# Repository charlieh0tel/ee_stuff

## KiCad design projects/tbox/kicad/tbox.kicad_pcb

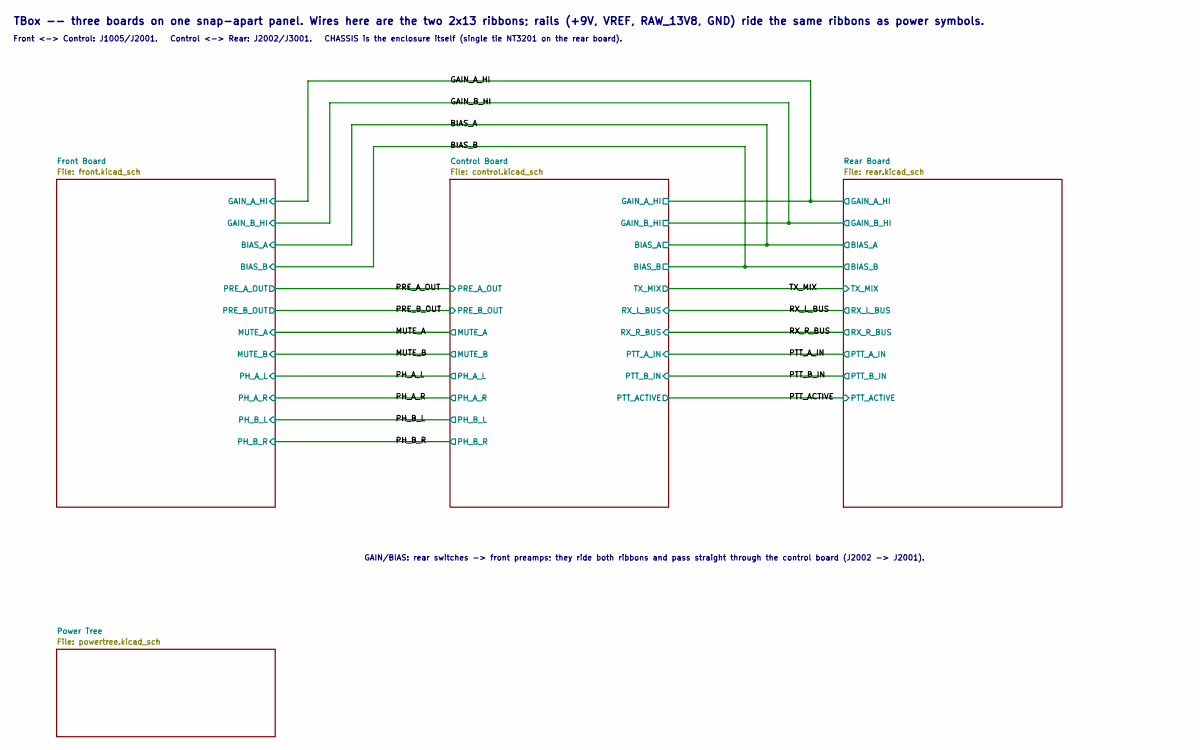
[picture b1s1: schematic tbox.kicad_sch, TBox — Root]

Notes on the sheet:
Front <-> Control: J1005/J2001. Control <-> Rear: J2002/J3001. CHASSIS is the enclosure itself (single tie NT3201 on the rear board).
GAIN/BIAS: rear switches -> front preamps; they ride both ribbons and pass straight through the control board (J2002 -> J2001).
TBox -- three boards on one snap-apart panel. Wires here are the two 2x13 ribbons; rails (+9V, VREF, RAW_13V8, GND) ride the same ribbons as power symbols.

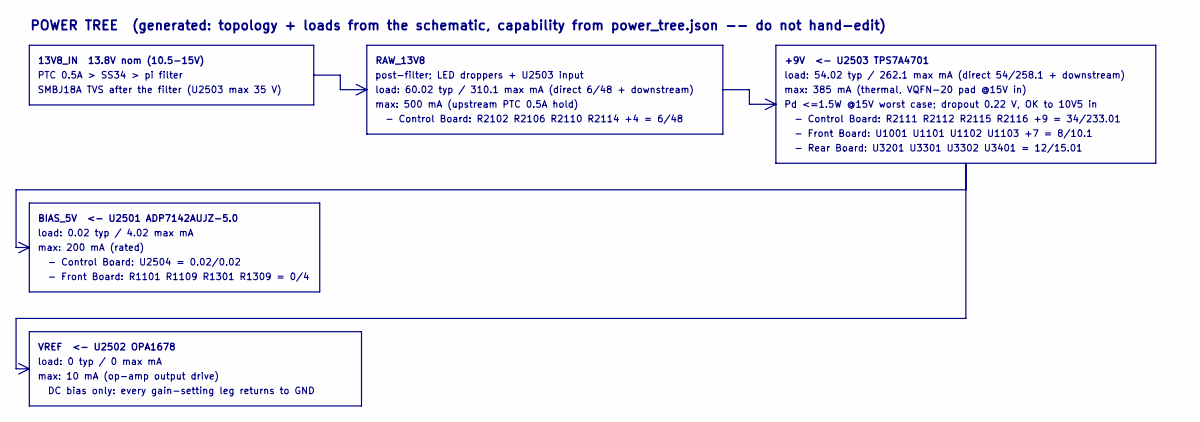
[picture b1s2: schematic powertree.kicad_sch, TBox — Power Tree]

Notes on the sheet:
POWER TREE (generated: topology + loads from the schematic, capability from power_tree.json -- do not hand-edit)
13V8_IN 13.8V nom (10.5-15V)
PTC 0.5A > SS34 > pi filter
SMBJ18A TVS after the filter (U2503 max 35 V)
RAW_13V8
post-filter; LED droppers + U2503 input
load: 60.02 typ / 310.1 max mA (direct 6/48 + downstream)
max: 500 mA (upstream PTC 0.5A hold)
- Control Board: R2102 R2106 R2110 R2114 +4 = 6/48
+9V <- U2503 TPS7A4701
load: 54.02 typ / 262.1 max mA (direct 54/258.1 + downstream)
max: 385 mA (thermal, VQFN-20 pad @15V in)
Pd <=1.5W @15V worst case; dropout 0.22 V, OK to 10V5 in
- Control Board: R2111 R2112 R2115 R2116 +9 = 34/233.01
- Front Board: U1001 U1101 U1102 U1103 +7 = 8/10.1
- Rear Board: U3201 U3301 U3302 U3401 = 12/15.01
BIAS_5V <- U2501 ADP7142AUJZ-5.0
load: 0.02 typ / 4.02 max mA
max: 200 mA (rated)
- Control Board: U2504 = 0.02/0.02
- Front Board: R1101 R1109 R1301 R1309 = 0/4
VREF <- U2502 OPA1678
load: 0 typ / 0 max mA
max: 10 mA (op-amp output drive)
DC bias only: every gain-setting leg returns to GND

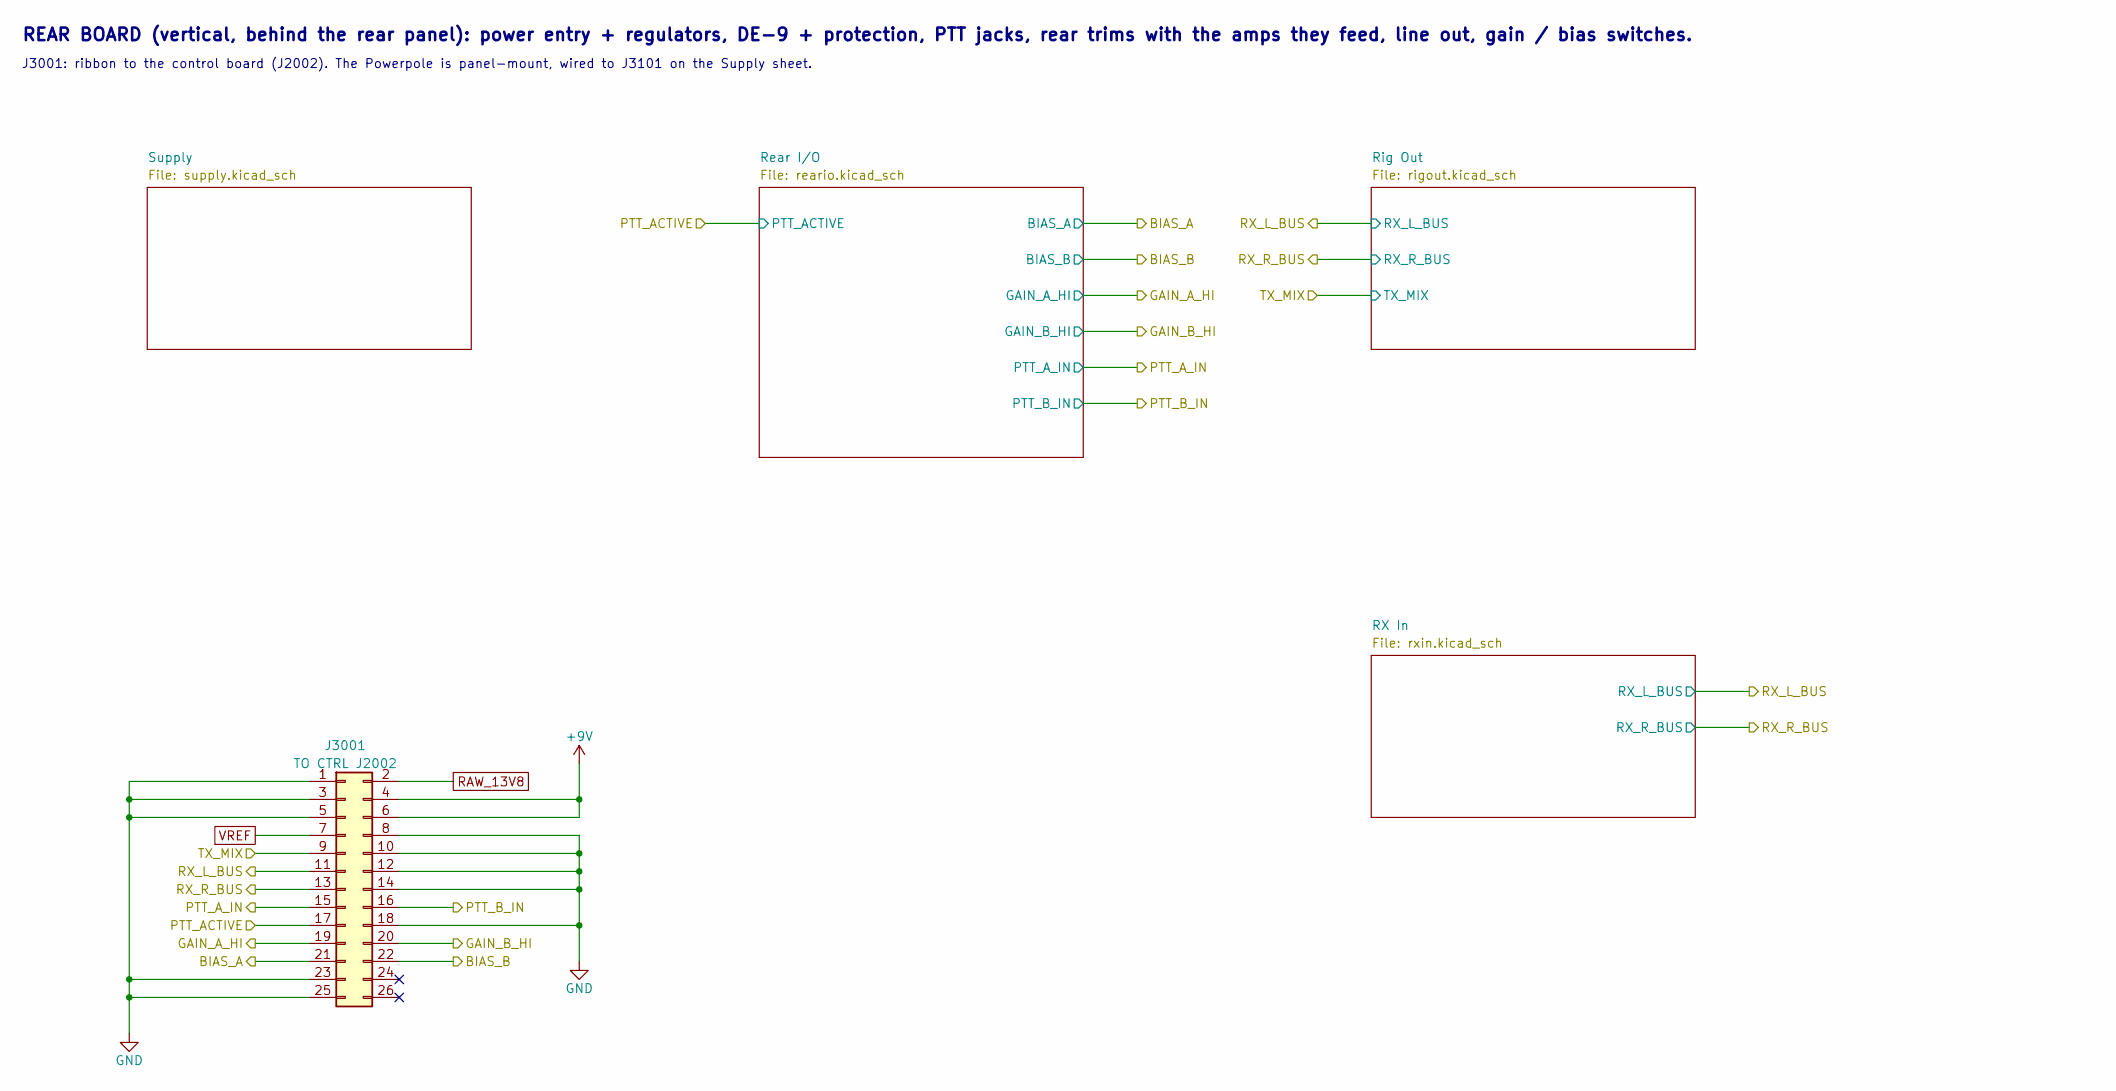
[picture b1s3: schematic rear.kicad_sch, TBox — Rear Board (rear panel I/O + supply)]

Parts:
J3001: TO CTRL J2002; IDC-Header_2x13_P2.54mm_Vertical; MPN IDC 2x13 box header

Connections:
+9V: J3001.4, J3001.6; also elsewhere on the board
/BIAS_A: J3001.21; also elsewhere on the board
/BIAS_B: J3001.22; also elsewhere on the board
/GAIN_A_HI: J3001.19; also elsewhere on the board
/GAIN_B_HI: J3001.20; also elsewhere on the board
/PTT_ACTIVE: J3001.17; also elsewhere on the board
/PTT_A_IN: J3001.15; also elsewhere on the board
/PTT_B_IN: J3001.16; also elsewhere on the board
/RX_L_BUS: J3001.11; also elsewhere on the board
/RX_R_BUS: J3001.13; also elsewhere on the board
/TX_MIX: J3001.9; also elsewhere on the board

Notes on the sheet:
REAR BOARD (vertical, behind the rear panel): power entry + regulators, DE-9 + protection, PTT jacks, rear trims with the amps they feed, line out, gain / bias switches.
J3001: ribbon to the control board (J2002). The Powerpole is panel-mount, wired to J3101 on the Supply sheet.

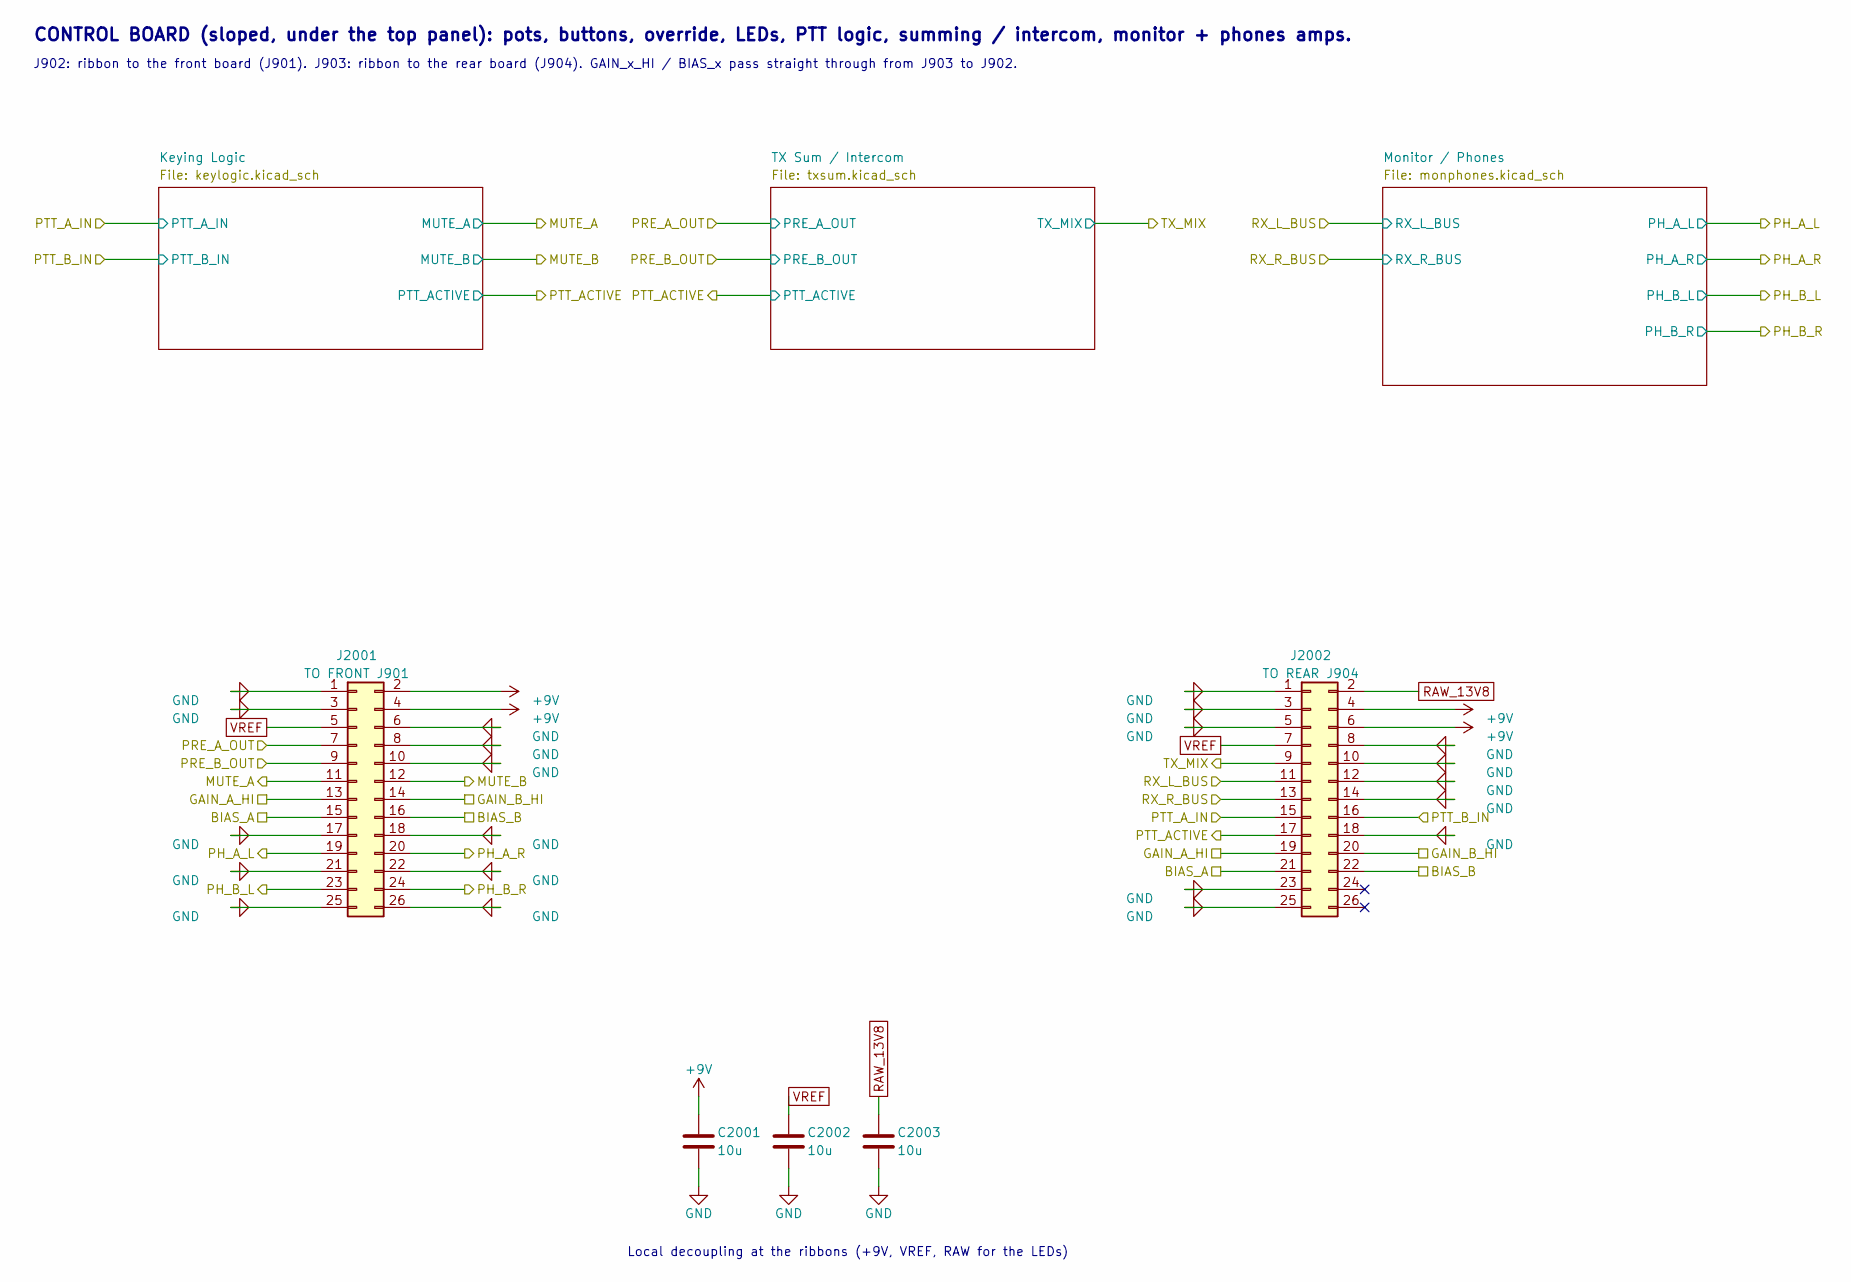
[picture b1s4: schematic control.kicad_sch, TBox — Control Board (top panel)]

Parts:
C2001, C2002, C2003: 10u
J2001: TO FRONT J901
J2002: TO REAR J904

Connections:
+9V: C2001.1, J2001.2, J2001.4, J2002.4, J2002.6; also elsewhere on the board
/BIAS_A: J2001.15, J2002.21; also elsewhere on the board
/BIAS_B: J2001.16, J2002.22; also elsewhere on the board
/GAIN_A_HI: J2001.13, J2002.19; also elsewhere on the board
/GAIN_B_HI: J2001.14, J2002.20; also elsewhere on the board
/MUTE_B: J2001.12; also elsewhere on the board
/PH_A_L: J2001.19; also elsewhere on the board
/PH_A_R: J2001.20; also elsewhere on the board
/PH_B_L: J2001.23; also elsewhere on the board
/PH_B_R: J2001.24; also elsewhere on the board
/PRE_A_OUT: J2001.7; also elsewhere on the board
/PRE_B_OUT: J2001.9; also elsewhere on the board
/PTT_ACTIVE: J2002.17; also elsewhere on the board
/PTT_A_IN: J2002.15; also elsewhere on the board
/PTT_B_IN: J2002.16; also elsewhere on the board
/RX_L_BUS: J2002.11; also elsewhere on the board
/RX_R_BUS: J2002.13; also elsewhere on the board
/TX_MIX: J2002.9; also elsewhere on the board

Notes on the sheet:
Local decoupling at the ribbons (+9V, VREF, RAW for the LEDs)
CONTROL BOARD (sloped, under the top panel): pots, buttons, override, LEDs, PTT logic, summing / intercom, monitor + phones amps.
J902: ribbon to the front board (J901). J903: ribbon to the rear board (J904). GAIN_x_HI / BIAS_x pass straight through from J903 to J902.

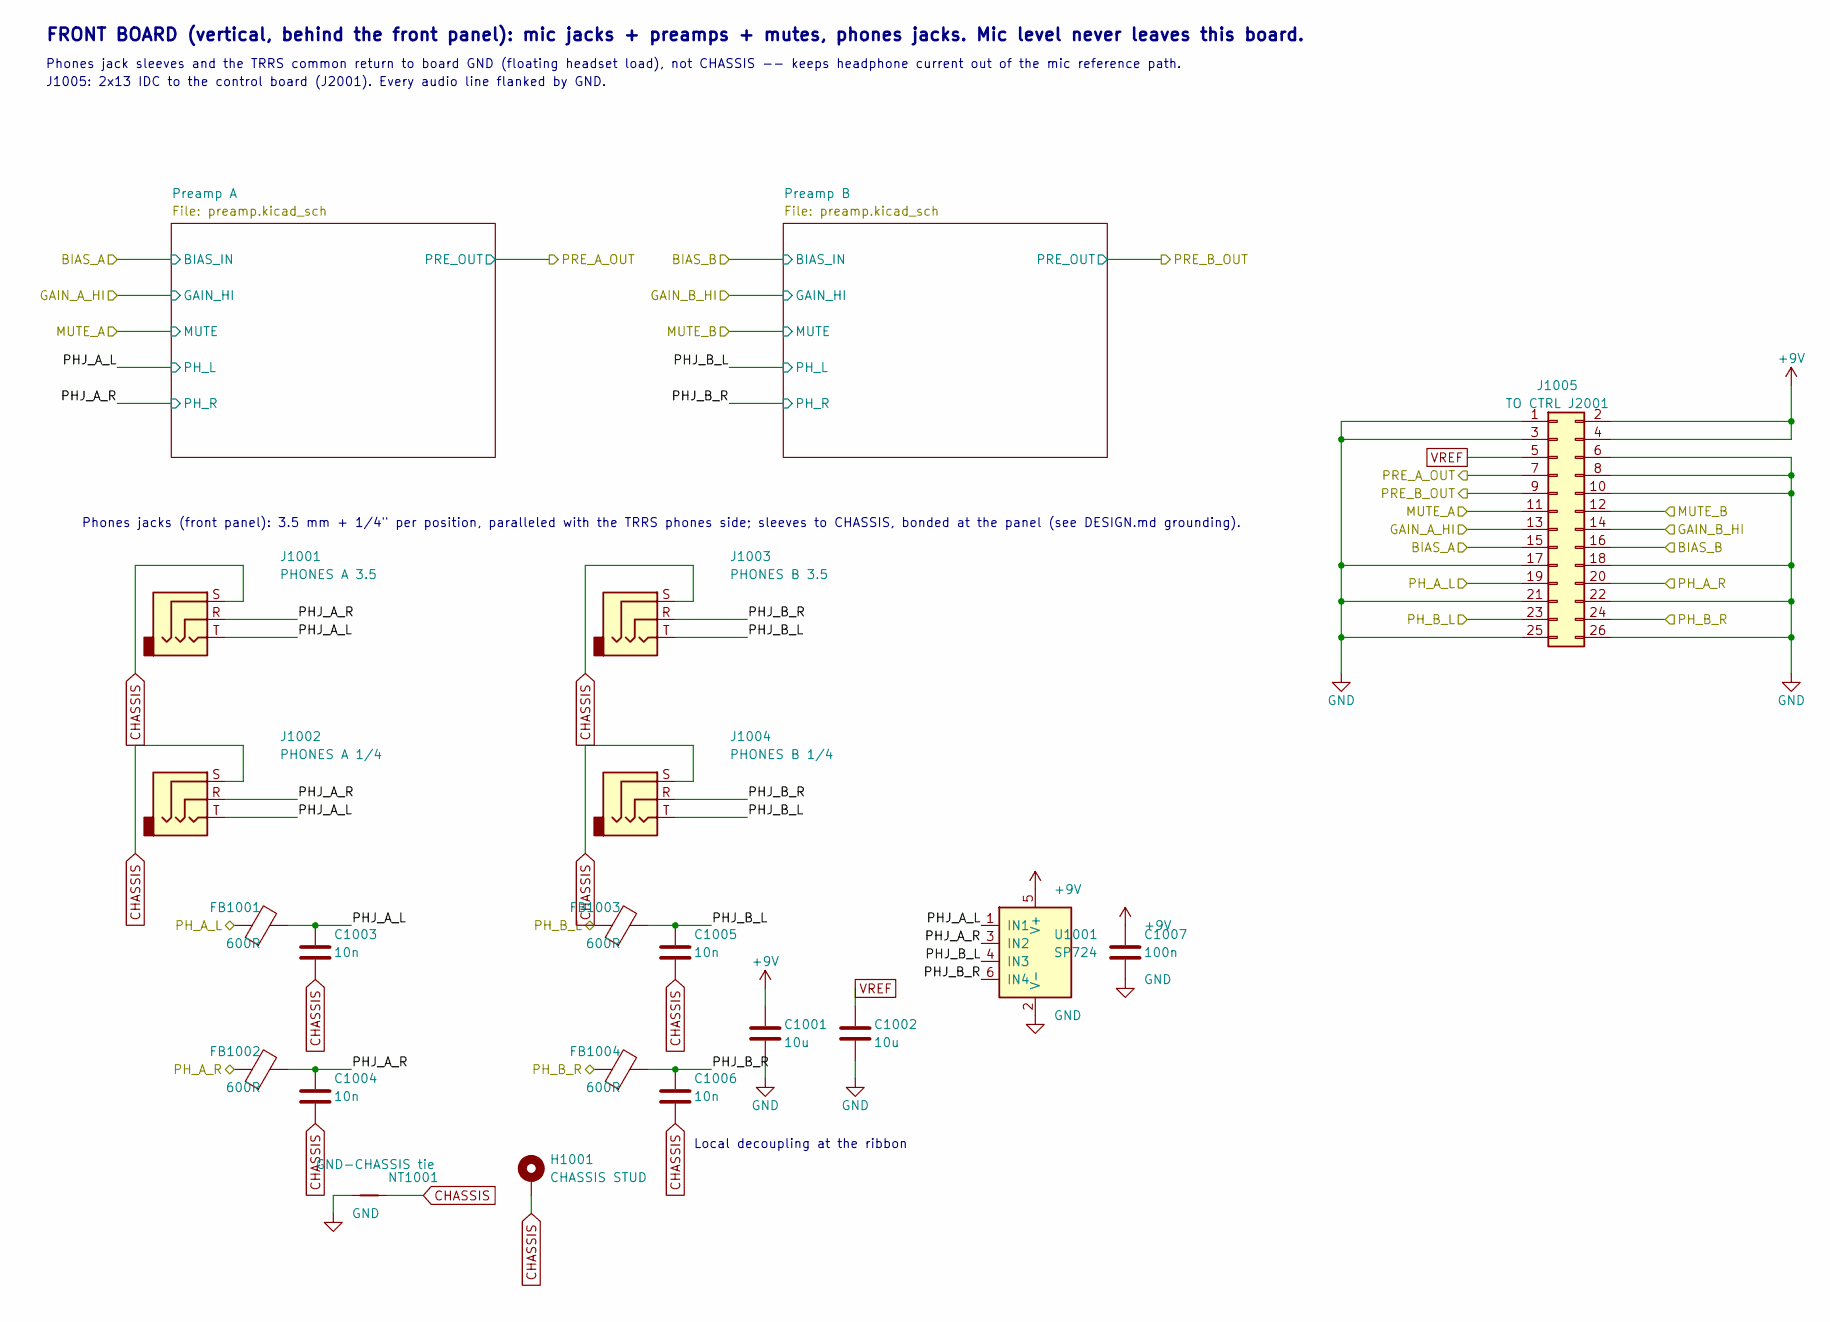
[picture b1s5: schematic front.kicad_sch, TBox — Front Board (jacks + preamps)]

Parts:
C1001, C1002: 10u; C_1206_3216Metric
C1003, C1004, C1005, C1006: 10n; C_0603_1608Metric
C1007: 100n; C_0603_1608Metric
FB1001, FB1002, FB1003, FB1004: 600R; L_0805_2012Metric; MPN BLM21PG601SN1D
H1001: CHASSIS STUD; MountingHole_3.2mm_M3_Pad
J1001: PHONES A 3.5; Jack_3.5mm_CUI_SJ1-3533NG_Horizontal; MPN SJ1-3533NG
J1002: PHONES A 1/4; Jack_6.35mm_Neutrik_NRJ6HF-1_Horizontal; MPN NRJ6HF-1
J1003: PHONES B 3.5; Jack_3.5mm_CUI_SJ1-3533NG_Horizontal; MPN SJ1-3533NG
J1004: PHONES B 1/4; Jack_6.35mm_Neutrik_NRJ6HF-1_Horizontal; MPN NRJ6HF-1
J1005: TO CTRL J2001; IDC-Header_2x13_P2.54mm_Vertical; MPN IDC 2x13 box header
NT1001: GND-CHASSIS tie; NetTie-2_SMD_Pad0.5mm
U1001: SP724; SOT-23-6; MPN SP724AHTG

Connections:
+9V: C1001.1, C1007.1, J1005.2, J1005.4, U1001.5 (V+); also elsewhere on the board
/BIAS_A: J1005.15; also elsewhere on the board
/BIAS_B: J1005.16; also elsewhere on the board
/Front Board/PHJ_A_L: C1003.1, FB1001.2, J1001.T, J1002.T, U1001.1 (IN1); also elsewhere on the board
/Front Board/PHJ_A_R: C1004.1, FB1002.2, J1001.R, J1002.R, U1001.3 (IN2); also elsewhere on the board
/Front Board/PHJ_B_L: C1005.1, FB1003.2, J1003.T, J1004.T, U1001.4 (IN3); also elsewhere on the board
/Front Board/PHJ_B_R: C1006.1, FB1004.2, J1003.R, J1004.R, U1001.6 (IN4); also elsewhere on the board
/GAIN_A_HI: J1005.13; also elsewhere on the board
/GAIN_B_HI: J1005.14; also elsewhere on the board
/MUTE_B: J1005.12; also elsewhere on the board
/PH_A_L: FB1001.1, J1005.19; also elsewhere on the board
/PH_A_R: FB1002.1, J1005.20; also elsewhere on the board
/PH_B_L: FB1003.1, J1005.23; also elsewhere on the board
/PH_B_R: FB1004.1, J1005.24; also elsewhere on the board
/PRE_A_OUT: J1005.7; also elsewhere on the board
/PRE_B_OUT: J1005.9; also elsewhere on the board

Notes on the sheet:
J1005: 2x13 IDC to the control board (J2001). Every audio line flanked by GND.
Phones jacks (front panel): 3.5 mm + 1/4" per position, paralleled with the TRRS phones side; sleeves to CHASSIS, bonded at the panel (see DESIGN.md grounding).
Phones jack sleeves and the TRRS common return to board GND (floating headset load), not CHASSIS -- keeps headphone current out of the mic reference path.
FRONT BOARD (vertical, behind the front panel): mic jacks + preamps + mutes, phones jacks. Mic level never leaves this board.
Local decoupling at the ribbon

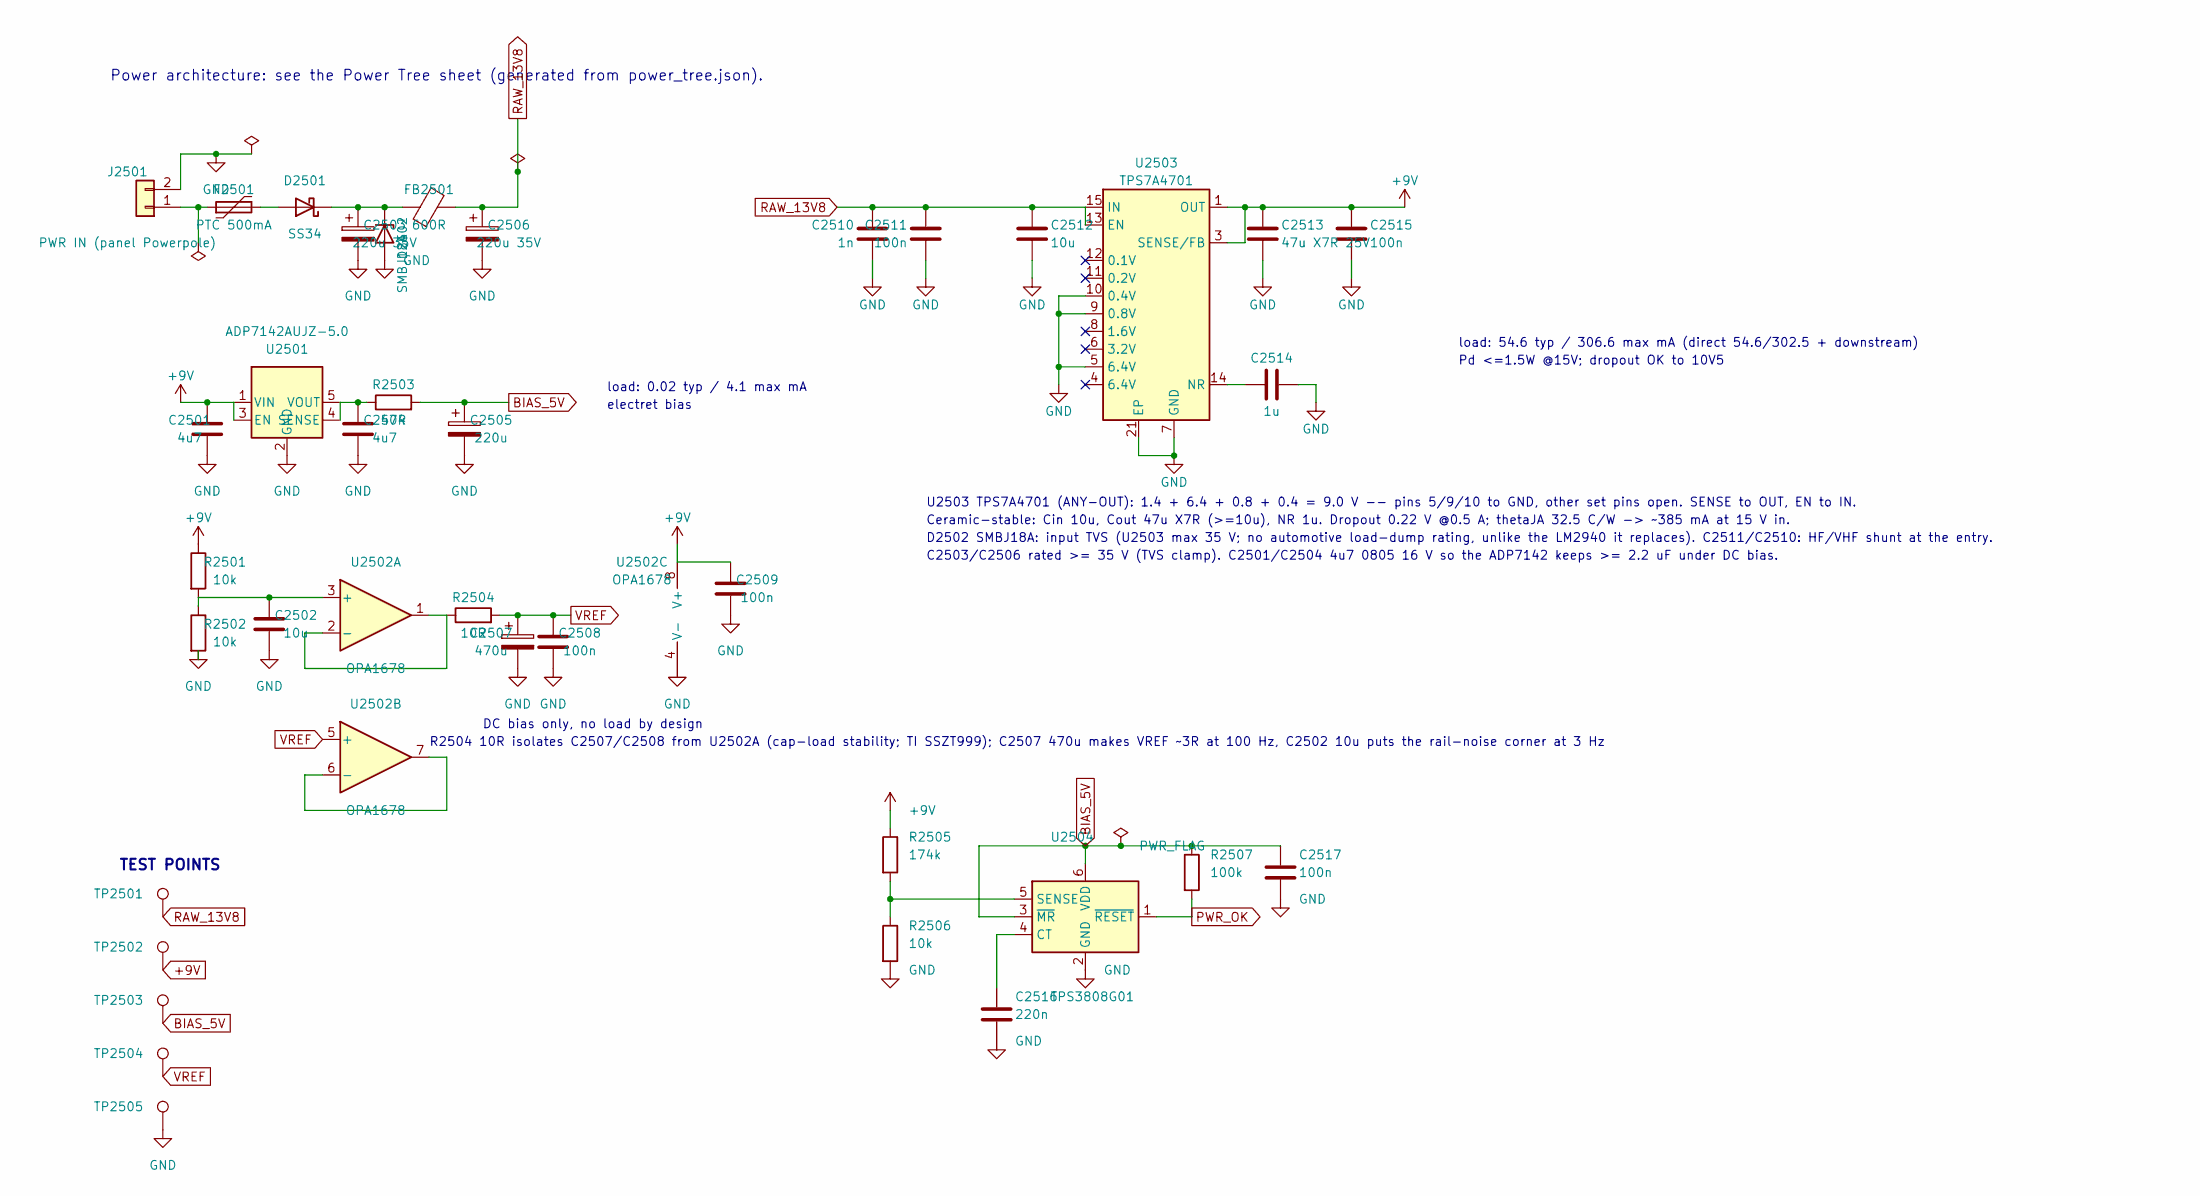
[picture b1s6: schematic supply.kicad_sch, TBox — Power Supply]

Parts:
C2501, C2504: 4u7; C_0805_2012Metric
C2502, C2512: 10u; C_1206_3216Metric
C2503, C2506: 220u 35V; CP_Elec_10x10.5
C2505: 220u; CP_Elec_8x10.5
C2507: 470u; CP_Elec_10x10.5
C2508, C2509, C2511, C2515, C2517: 100n; C_0603_1608Metric
C2510: 1n; C_0603_1608Metric
C2513: 47u X7R 25V; C_1210_3225Metric; MPN GRM32ER71E476KE15L
C2514: 1u; C_0603_1608Metric
C2516: 220n; C_0603_1608Metric
D2501: SS34; D_SMA; MPN SS34
D2502: SMBJ18A; D_SMB; MPN SMBJ18A
F2501: PTC 500mA; Fuse_1812_4532Metric; MPN 1812L050/60MR
FB2501: 600R; L_0805_2012Metric; MPN BLM21PG601SN1D
J2501: PWR IN (panel Powerpole); JST_XH_B2B-XH-A_1x02_P2.50mm_Vertical; MPN B2B-XH-A
R2501, R2502, R2506: 10k; R_0603_1608Metric
R2503: 47R; R_0603_1608Metric
R2504: 10R; R_0603_1608Metric
R2505: 174k; R_0603_1608Metric
R2507: 100k; R_0603_1608Metric
TP2501, TP2502, TP2503, TP2504, TP2505: TestPoint; TestPoint_Keystone_5015_Micro_Mini; MPN 5015
U2501: ADP7142AUJZ-5.0; TSOT-23-5; MPN ADP7142AUJZ-5.0-R7
U2502: OPA1678; SOIC-8_3.9x4.9mm_P1.27mm; MPN OPA1678IDR
U2503: TPS7A4701; Texas_RGW0020A_VQFN-20-1EP_5x5mm_P0.65mm_EP3.15x3.15mm_Ther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; MPN TPS7A4701RGWR
U2504: TPS3808G01; SOT-23-6; MPN TPS3808G01DBVR

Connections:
+9V: C2501.1, C2509.1, C2513.1, C2515.1, R2501.1, R2505.1, TP2502.1 (1_1), U2501.1 (VIN), U2501.3 (EN), U2502.8 (V+), U2503.1 (OUT), U2503.3 (SENSE/FB), U2503.20 (OUT); also elsewhere on the board
unnamed: D2501.2 (A), F2501.2
unnamed: C2503.1, D2501.1 (K), D2502.1 (K), FB2501.1
unnamed: F2501.1, J2501.1
unnamed: C2504.1, R2503.1, U2501.4 (SENSE), U2501.5 (VOUT)
unnamed: C2502.1, R2501.2, R2502.1, U2502.3 (+)
unnamed: R2504.1, U2502.1, U2502.2 (-)
unnamed: U2502.6 (-), U2502.7
unnamed: C2514.1, U2503.14 (NR)
unnamed: C2516.1, U2504.4 (CT)
unnamed: R2505.2, R2506.1, U2504.5 (SENSE)
PWR_OK: R2507.2, U2504.1 (~RESET); also elsewhere on the board

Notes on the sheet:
Ceramic-stable: Cin 10u, Cout 47u X7R (>=10u), NR 1u. Dropout 0.22 V @0.5 A; thetaJA 32.5 C/W -> ~385 mA at 15 V in.
R2504 10R isolates C2507/C2508 from U2502A (cap-load stability; TI SSZT999); C2507 470u makes VREF ~3R at 100 Hz, C2502 10u puts the rail-noise corner at 3 Hz
C2503/C2506 rated >= 35 V (TVS clamp). C2501/C2504 4u7 0805 16 V so the ADP7142 keeps >= 2.2 uF under DC bias.
U2503 TPS7A4701 (ANY-OUT): 1.4 + 6.4 + 0.8 + 0.4 = 9.0 V -- pins 5/9/10 to GND, other set pins open. SENSE to OUT, EN to IN.
Power architecture: see the Power Tree sheet (generated from power_tree.json).
D2502 SMBJ18A: input TVS (U2503 max 35 V; no automotive load-dump rating, unlike the LM2940 it replaces). C2511/C2510: HF/VHF shunt at the entry.
TEST POINTS
Pd <=1.5W @15V; dropout OK to 10V5
load: 54.6 typ / 306.6 max mA (direct 54.6/302.5 + downstream)
electret bias
load: 0.02 typ / 4.1 max mA
DC bias only, no load by design

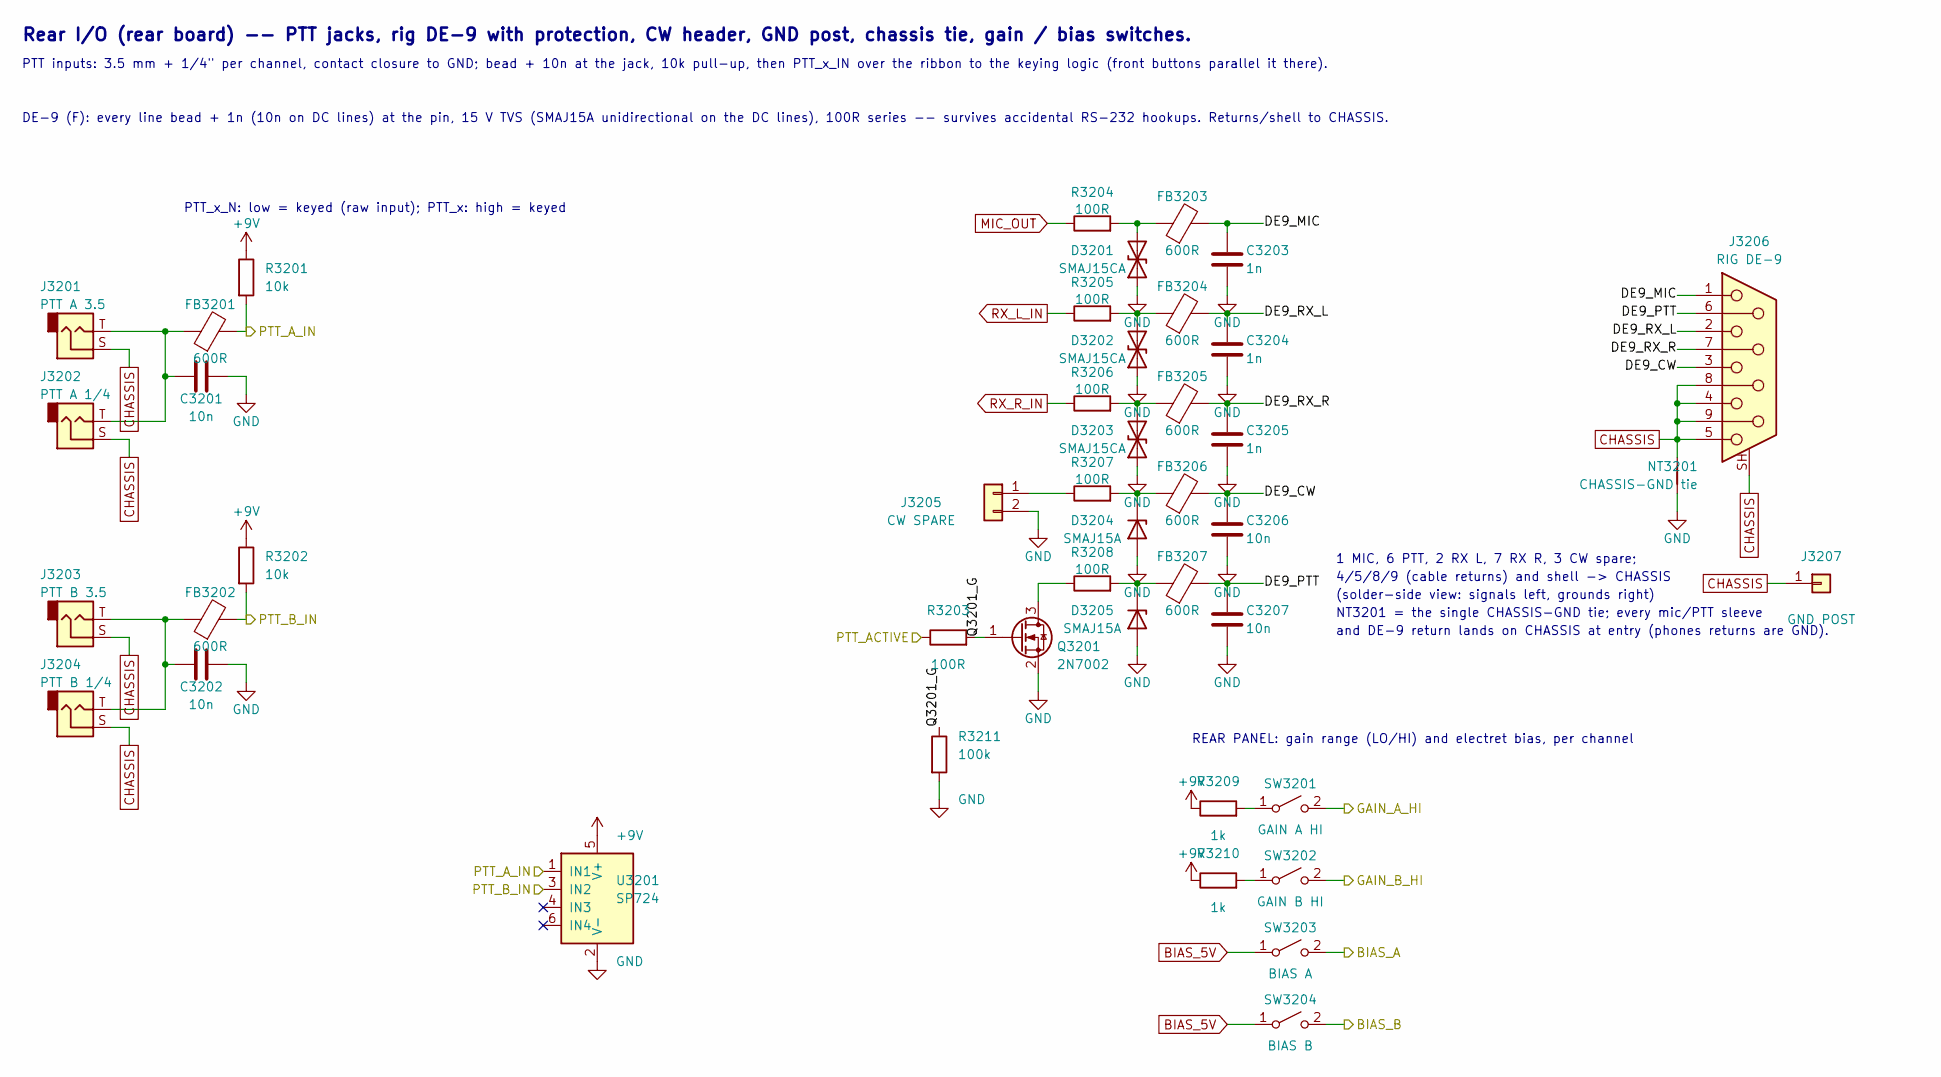
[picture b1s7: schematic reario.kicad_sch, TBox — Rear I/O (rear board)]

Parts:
C3201, C3202, C3206, C3207: 10n; C_0603_1608Metric
C3203, C3204, C3205: 1n; C_0603_1608Metric
D3201, D3202, D3203: SMAJ15CA; D_SMA; MPN SMAJ15CA
D3204, D3205: SMAJ15A; D_SMA; MPN SMAJ15A
FB3201, FB3202, FB3203, FB3204, FB3205, FB3206, FB3207: 600R; L_0805_2012Metric
J3201: PTT A 3.5; Jack_3.5mm_Switchcraft_35RAPCxxH3_Horizontal; MPN 35RAPC2AH3
J3202: PTT A 1/4; Jack_6.35mm_Neutrik_NRJ6HM-1-PRE_Horizontal; MPN NRJ6HM-1-PRE
J3203: PTT B 3.5; Jack_3.5mm_Switchcraft_35RAPCxxH3_Horizontal; MPN 35RAPC2AH3
J3204: PTT B 1/4; Jack_6.35mm_Neutrik_NRJ6HM-1-PRE_Horizontal; MPN NRJ6HM-1-PRE
J3205: CW SPARE; PinHeader_1x02_P2.54mm_Vertical
J3206: RIG DE-9; DSUB-9_Socket_Horizontal_P2.77x2.84mm_EdgePinOffset7.70mm_H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
J3207: GND POST
NT3201: CHASSIS-GND tie; NetTie-2_SMD_Pad0.5mm
Q3201: 2N7002; SOT-23; MPN 2N7002
R3201, R3202: 10k; R_0603_1608Metric
R3203, R3204, R3205, R3206, R3207, R3208: 100R; R_0603_1608Metric
R3209, R3210: 1k; R_0603_1608Metric
R3211: 100k; R_0603_1608Metric
SW3201: GAIN A HI; SW_Toggle_CK_7101_AV2_Horizontal; MPN 7101MD9AV2BE
SW3202: GAIN B HI; SW_Toggle_CK_7101_AV2_Horizontal; MPN 7101MD9AV2BE
SW3203: BIAS A; SW_Toggle_CK_7101_AV2_Horizontal; MPN 7101MD9AV2BE
SW3204: BIAS B; SW_Toggle_CK_7101_AV2_Horizontal; MPN 7101MD9AV2BE
U3201: SP724; SOT-23-6; MPN SP724AHTG

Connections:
+9V: R3201.1, R3202.1, R3209.1, R3210.1, U3201.5 (V+); also elsewhere on the board
/BIAS_A: SW3203.2 (B); also elsewhere on the board
/BIAS_B: SW3204.2 (B); also elsewhere on the board
/GAIN_A_HI: SW3201.2 (B); also elsewhere on the board
/GAIN_B_HI: SW3202.2 (B); also elsewhere on the board
/PTT_ACTIVE: R3203.1; also elsewhere on the board
/PTT_A_IN: FB3201.2, R3201.2, U3201.1 (IN1); also elsewhere on the board
/PTT_B_IN: FB3202.2, R3202.2, U3201.3 (IN2); also elsewhere on the board
/Rear Board/Rear I/O/DE9_CW: C3206.1, FB3206.2, J3206.3
/Rear Board/Rear I/O/DE9_MIC: C3203.1, FB3203.2, J3206.1
/Rear Board/Rear I/O/DE9_PTT: C3207.1, FB3207.2, J3206.6
/Rear Board/Rear I/O/DE9_RX_L: C3204.1, FB3204.2, J3206.2
/Rear Board/Rear I/O/DE9_RX_R: C3205.1, FB3205.2, J3206.7
/Rear Board/Rear I/O/Q3201_G: Q3201.1 (G), R3203.2, R3211.1
MIC_OUT: R3204.1; also elsewhere on the board
unnamed: C3201.1, FB3201.1, J3201.T, J3202.T
unnamed: C3202.1, FB3202.1, J3203.T, J3204.T
unnamed: D3201.2 (A2), FB3203.1, R3204.2
unnamed: D3202.2 (A2), FB3204.1, R3205.2
unnamed: D3203.2 (A2), FB3205.1, R3206.2
unnamed: D3204.1 (K), FB3206.1, R3207.2
unnamed: D3205.1 (K), FB3207.1, R3208.2
unnamed: J3205.1, R3207.1
unnamed: Q3201.3 (D), R3208.1
unnamed: R3209.2, SW3201.1 (A)
unnamed: R3210.2, SW3202.1 (A)
RX_L_IN: R3205.1; also elsewhere on the board
RX_R_IN: R3206.1; also elsewhere on the board

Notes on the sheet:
REAR PANEL: gain range (LO/HI) and electret bias, per channel
(solder-side view: signals left, grounds right)
NT3201 = the single CHASSIS-GND tie; every mic/PTT sleeve
DE-9 (F): every line bead + 1n (10n on DC lines) at the pin, 15 V TVS (SMAJ15A unidirectional on the DC lines), 100R series -- survives accidental RS-232 hookups. Returns/shell to CHASSIS.
1 MIC, 6 PTT, 2 RX L, 7 RX R, 3 CW spare;
PTT_x_N: low = keyed (raw input); PTT_x: high = keyed
4/5/8/9 (cable returns) and shell -> CHASSIS
PTT inputs: 3.5 mm + 1/4" per channel, contact closure to GND; bead + 10n at the jack, 10k pull-up, then PTT_x_IN over the ribbon to the keying logic (front buttons parallel it there).
Rear I/O (rear board) -- PTT jacks, rig DE-9 with protection, CW header, GND post, chassis tie, gain / bias switches.
and DE-9 return lands on CHASSIS at entry (phones returns are GND).

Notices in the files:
projects/canob/canob.kicad_pcb:
(C) 2025 Impulse Labs
